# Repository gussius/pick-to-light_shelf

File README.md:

# pick-to-light_shelf
Pick-to-Light shelf node, this board communicates with the web server on the local network, receives bin quantities, and passes this info onto the bin nodes over i2c network.

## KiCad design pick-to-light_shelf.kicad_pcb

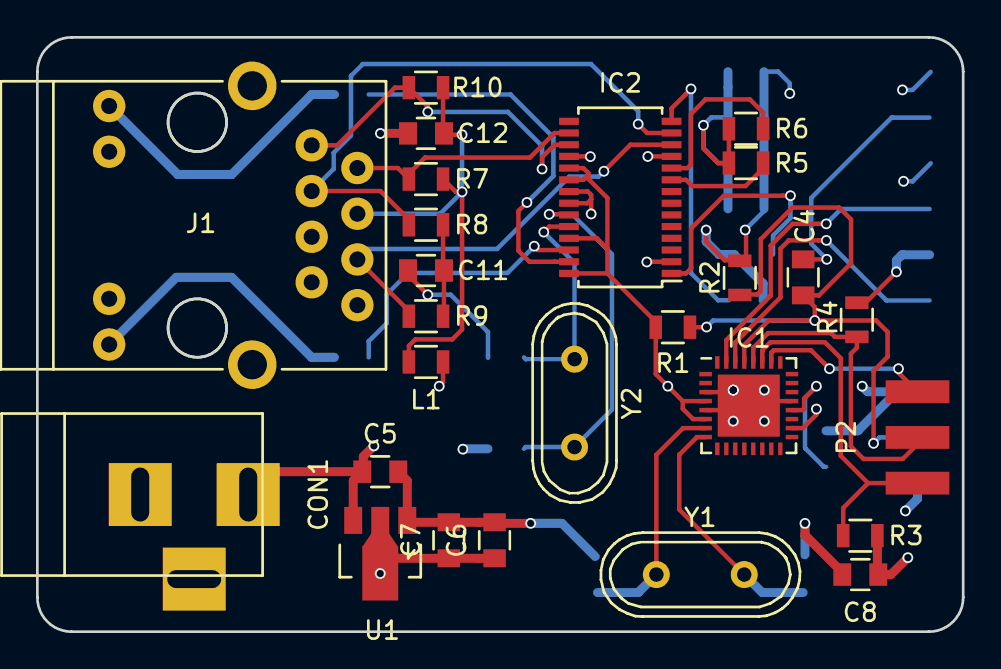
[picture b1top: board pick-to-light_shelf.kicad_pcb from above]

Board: 4 copper layers, 51.4 x 33.0 mm, 40 parts (0 on the bottom side), 29 nets.

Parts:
C1, C2: 15pF; C_0805
C3, C4, C7: 0.1uF; C_0805
C5: 10uF; C_0805
C6: 22uF; C_0805
C8, C12, C14, C15, C16, C17: 100nF; C_0805
C9, C10: 10pF; C_0805
C11: 10nF; C_0805
C13: 10uF; C_1206
CON1: 7.5V; BARREL_JACK
IC1: ATMEGA168PA-A; QFN-32-1EP_5x5mm_Pitch0.5mm
IC2: ENC28J60-C/SS; TSSOP-28_4.4x9.7mm_Pitch0.65mm
J1: RJ45-TRANSFO; HR911105A
L1: VAL; R_0805
P1: prog_smd_pads
P2: 2x3-male-pin-header-smd-board-edge
R1, R6: 10k; R_0805
R2: 0; R_0805
R3, R4: 22k; R_0805
R5: 100k; R_0805
R7, R8, R9, R10: 49.9; R_0805
R11, R12: 180; R_0805
R13: 2k; R_0805
U1: LD1117S33TR; SOT89-3_Housing
Y1: Crystal; Crystal_HC49-U_Vertical
Y2: 25MHz; Crystal_HC49-U_Vertical

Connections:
/A3: IC1.26, P2.5
/A4: IC1.27, P2.1, R3.2
/A5: IC1.28, P2.3, R4.2
/CS: IC2.9, R5.2
/LEDA: IC2.27, R11.1
/LEDB: IC2.26, R12.1
/RAW: C5.1, CON1.1, P2.2, U1.3
/RESET: C4.1, IC1.29, P2.4, R1.2, R2.2
/RST: IC2.10, R6.2
/RX1: IC1.30, P1.6
/TPIN+: IC2.13, J1.3, R8.1
/TPIN-: IC2.12, J1.6, R9.1
/TPOUT+: IC2.17, J1.1, R10.1
/TPOUT-: IC2.16, J1.2, R7.1
/TX0: IC1.31, P1.4
/XTAL1: C1.1, IC1.7, Y1.1
/XTAL2: C2.1, IC1.8, Y1.2
GND: C1.2, C2.2, C3.2, C5.2, C6.2, C7.2, C8.2, C9.2, C10.2, C11.2, C12.1, C13.2, C14.2, C15.2, C16.2, C17.2, CON1.2, IC1.3, IC1.5, IC1.21, IC2.2, IC2.11, IC2.18, IC2.21, IC2.22, J1.8, J1.10, J1.11, J1.13, P1.1, P1.3, P2.6, R2.1, R13.2, U1.1
unnamed: C3.1, IC1.20
unnamed: C4.2, P1.2
unnamed: C9.1, IC2.23, Y2.1
unnamed: C10.1, IC2.24, Y2.2
unnamed: C11.1, R8.2, R9.2
unnamed: C12.2, J1.4, L1.2, R7.2, R10.2
unnamed: C13.1, IC2.1
unnamed: IC2.14, R13.1
unnamed: J1.9, R11.2
unnamed: J1.12, R12.2
VCC: C6.1, C7.1, C8.1, C14.1, C15.1, C16.1, C17.1, IC1.4, IC1.6, IC1.18, IC2.15, IC2.19, IC2.20, IC2.25, IC2.28, L1.1, P1.5, R1.1, R3.1, R4.1, R5.1, R6.1, U1.2

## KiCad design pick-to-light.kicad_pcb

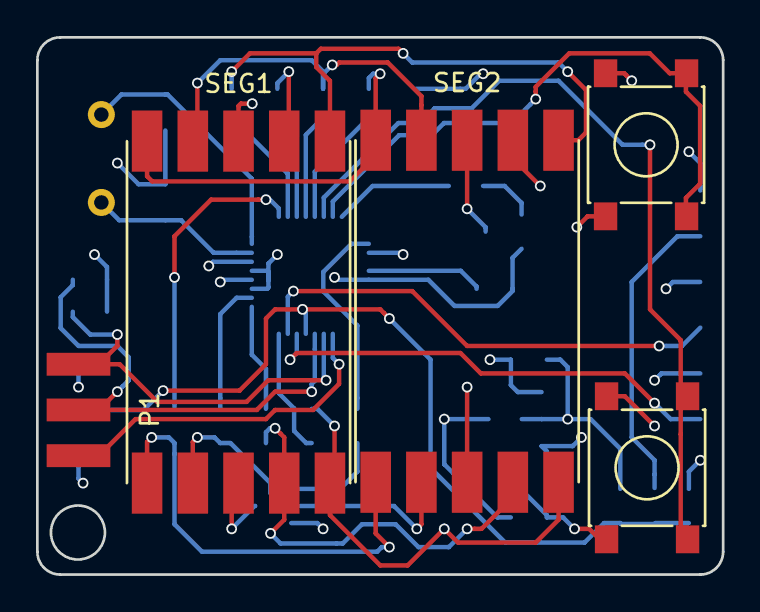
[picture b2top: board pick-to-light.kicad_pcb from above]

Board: 4 copper layers, 38.1 x 29.8 mm, 34 parts (0 on the bottom side), 37 nets.

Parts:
C2, C5: 0.1uF; C_0805
C3: 10uF; C_0805
C4: 22uF; C_0805
C6: 0.1uF; C_0805_HandSoldering
C7, C8: C; C_0805
IC1: ATMEGA168PA-A; LQFP-32_5x5mm_Pitch0.5mm
P1: CONN_02X03; 2x3-male-pin-header-smd-board-edge
P2: CONN_02X03; prog_smd_pads
Q1, Q2: BC849; SOT-23
R1, R2, R3, R4, R5, R6, R7, R8: 110; R_0805
R9, R12: 4K7; R_0805
R10, R11, R15: 10k; R_0805
R13, R14: 22k; R_0805
R16: 0; C_0603_HandSoldering
SEG1, SEG2: HDSP-C5A3; ACSC56-41SRWA-F01
SW1, SW2: SW_PUSH; SW_SPST_PTS645
U1: LD1117S33TR; SOT89-3_Housing
Y1: Crystal; Crystal_HC49-U_Vertical

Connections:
A3: IC1.26, P1.5
A4: IC1.27, P1.1, R13.2
A5: IC1.28, P1.3, R14.2
GND: C2.2, C3.2, C4.2, C5.2, C7.2, C8.2, IC1.3, IC1.5, IC1.21, P1.6, P2.1, P2.3, Q1.2, Q2.2, R16.1, SW1.2, SW2.2, U1.1
unnamed: C2.1, IC1.20
unnamed: C6.2, P2.2
unnamed: IC1.1, R7.2
unnamed: IC1.2, R6.2
unnamed: IC1.9, R5.2
unnamed: IC1.10, R4.2
unnamed: IC1.11, R3.2
unnamed: IC1.12, R2.2
unnamed: IC1.13, R1.2
unnamed: IC1.14, R11.1, SW1.1
unnamed: IC1.15, R10.1, SW2.1
unnamed: IC1.16, R12.2
unnamed: IC1.17, R9.2
unnamed: IC1.32, R8.2
unnamed: Q1.1, R9.1
unnamed: Q1.3, SEG1.3, SEG1.8
unnamed: Q2.1, R12.1
unnamed: Q2.3, SEG2.3, SEG2.8
unnamed: R1.1, SEG1.10, SEG2.10
unnamed: R2.1, SEG1.9, SEG2.9
unnamed: R3.1, SEG1.7, SEG2.7
unnamed: R4.1, SEG1.6, SEG2.6
unnamed: R5.1, SEG1.1, SEG2.1
unnamed: R6.1, SEG1.2, SEG2.2
unnamed: R7.1, SEG1.4, SEG2.4
unnamed: R8.1, SEG1.5, SEG2.5
RAW: C3.1, P1.2, U1.3
RESET: C6.1, IC1.29, P1.4, R15.2, R16.2
RX1: IC1.30, P2.6
TX0: IC1.31, P2.4
VCC: C4.1, C5.1, IC1.4, IC1.6, IC1.18, P2.5, R10.2, R11.2, R13.1, R14.1, R15.1, U1.2
XTAL1: C7.1, IC1.7, Y1.1
XTAL2: C8.1, IC1.8, Y1.2

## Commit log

2015-12-03 Added pick-to-light project to git for first time
2015-12-03 Started to hack the node design for custom ATMEGA168P circuit
2015-12-03 Fleshing out the circuit, need to check against pro mini reference and actual board design
2015-12-03 Added pdf printout for reference on this commit
2015-12-03 Added power supply circuit to schematic
2015-12-07 Completed first itteration of layout. Needs spacing out and rerouting.
2015-12-07 Finished second round of layout.
2015-12-07 3d models updated, schematic pdf updated.
2015-12-13 Updated description for shelf node.
2015-12-16 Completed schematic, started pcb layout
2018-10-28 Getting things up to date to start on project again
